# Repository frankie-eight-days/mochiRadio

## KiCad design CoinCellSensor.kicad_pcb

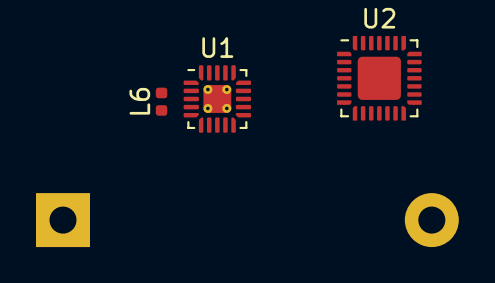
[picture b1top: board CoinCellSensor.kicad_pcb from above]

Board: 2 copper layers, 4 parts (1 on the bottom side), 5 nets, no tracks yet.

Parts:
BT1: Battery_Cell; BatteryHolder_Keystone_107_1x23mm
L6: 18nH; L_0402_1005Metric
U1: SI4455; VQFN-20-1EP_3x3mm_P0.45mm_EP1.55x1.55mm_ThermalVias
U2: ATmega328P-MMH; QFN-28-1EP_4x4mm_P0.45mm_EP2.4x2.4mm

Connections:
+3V3: BT1.1, U1.7, U1.8
GND: BT1.2, U1.1, U1.6, U1.9
unnamed: L6.2, U1.3
unnamed: L6.1, U1.4
unnamed: U2.4, U2.18, U2.29

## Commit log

2019-08-16 Initial commit. Components, footprints and layout need to be done for rev 1
    Brain dump
